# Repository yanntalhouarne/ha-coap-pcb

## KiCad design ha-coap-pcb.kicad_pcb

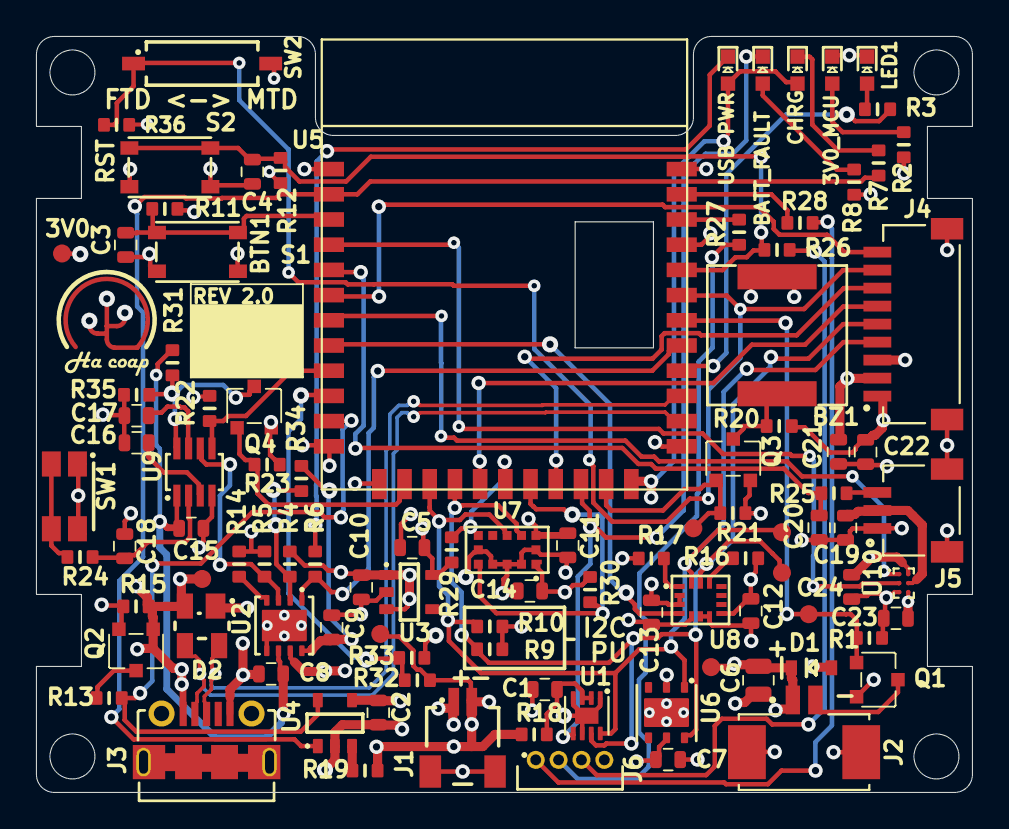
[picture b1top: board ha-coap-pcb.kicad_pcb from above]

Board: 4 copper layers, 52.0 x 42.0 mm, 104 parts (0 on the bottom side), 58 nets.

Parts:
BZ1: CPT-7502-65-SMT-TR; CPT-7502-65-SMT-TR-Footprint-1
C1, C3, C4, C7, C8, C9, C12, C13, C14, C15, C18, C20, C23, C24: C0603C104K5RACTU; C0603
C2, C5, C10, C19, C21, C22: CL10A105KB8NNNC; C0603
C6: GRM21BR61H106KE43L; C0805
C11: CL10A475KP8NNNC; C0603
C16, C17: CC0603KRX7R9BB333; C0603
D1: SD05T1G; SD05T1G-Footprint-1
D2: SP0503BAHTG; SP0503BAHTG-Footprint-1
J1: SM02B-SRSS-TB; FP-SM02B-SRSS-TB_LF_SN-0
J2: 0532610271; 0532610271-Footprint-1
J3: USB-MICRO-1050170001; USB-MICRO-B_V
J4: SM09B-SRSS-TB; SM09B-SRSS-TB-Footprint-1
J5: SM03B-SRSS-TB; SM03B-SRSS-TB-Footprint-1
J6: M50-3930442; FP-M50-3930442-MFG
LED1: LTST-C190GKT; LED-0603
LED2: LTST-C190TBKT; LED-0603
LED3: LTST-C190KRKT; LED-0603
LED4: LTST-C190KFKT; LED-0603
LED5: LTST-C190KSKT; LED-0603
M1, M2, M3, M4: MH-2.5mm-Non-Plated; MH-2.5mm-Non-Plated-Footprint-1
Q1: TSM850N06CX RFG; SOT-23-3
Q2, Q3, Q4: 2N7002P,235; SOT-23-3
R1, R15, R21, R23: RMCF0603FT47K0; R0603
R2, R3, R6, R7, R8, R20, R25: RMCF0603FT1K00; R0603
R4, R5, R11, R12, R22, R29, R30, R33, R34, R36: RMCF0603FT10K0; R0603
R9, R10, R24, R32: RMCF0603FT4K70; R0603
R13: RMCF0603FT2K00; R0603
R14: RMCF0603FG402R; R0603
R16, R17, R18, R19, R26, R27, R28: RMCF0603ZT0R00; R0603
R31: RMCF0603FT330K; R0603
R35: RMCF0603FT76K8; R0603
S1, S2: E-SWITCH_TL3365AF180QG_TACT-SWITCH-SMD; J_E-SWITCH_TL3365AF180QG_TACT-SWITCH-SMD
SW1: EVQ-P7A01P; FP-EVQ-P7A01P-MFG
SW2: TDA01H0SB1R; FP-TDA01H0SB1R-MFG
TP1, TP2, TP3, TP4, TP5, TP6, TP7, TP8: 1MM_PAD_TP; 1MM_PAD_TP-Footprint-1
U1: MAX17048G+T10; 8-WFDFN Exposed Pad
U2: TPS2115ADRBT; 8-VDFN (3x3) w/ EPAD
U3: S-1318D30-M5T1U4; SOT23-5
U4: STC4054GR; SOT23-5
U5: ACN52840; ACN52840-Footprint-1
U6: HDC1080DMBT; FP-DMB0006A-MFG
U7: VL53L0CXV0DH/1; FP-LGA-12-MFG
U8: LSM6DSMTR; 14-LGA (2.5x3mm)
U9: LTC2950CTS8-2#TRMPBF; SOT23-8
U10: FPF1320UCX; 6-WLCSP (0.96x1.66)

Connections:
+VBATT: C8.2, C15.1, J1.2, R18.1, R19.2, R31.2, R32.1, TP1.1, U2.6, U9.1
+VCC: BZ1.1, C6.2, C10.1, C22.1, C24.2, D1.2, J2.1, J4.1, R4.2, R20.2, TP4.1, U2.7, U3.1, U3.3, U10.A2
+VMCU: C5.1, C7.1, C11.1, C12.1, C13.1, C14.1, C21.1, C23.2, J4.2, R2.2, R8.2, R9.2, R10.2, R11.2, R12.2, R16.2, R22.2, R29.1, R30.2, R36.1, TP5.1, U3.5, U5.12, U5.24, U5.32, U6.5, U7.1, U7.11, U8.5, U8.8, U10.C2
+VSENSOR: C19.1, J5.2, U10.B2
+VUSB: C2.1, C9.2, D2.2, J3.1, LED4.2, LED5.2, Q2.1, R15.2, R34.2, TP6.1, U2.8, U4.4, U5.23
ALERTn: LED3.1, U1.5, U5.21
AN0: C20.2, R25.1, U5.5
AN1: J4.9, U5.6
BTN: C3.1, R11.1, S1.3, S1.4, U5.3
BUZZER: Q3.1, R21.1, TP8.1, U5.22
CHRGn: R7.2, U4.1, U5.2
D_N: D2.3, J3.2, U5.25
D_P: D2.4, J3.3, U5.26
GND: C1.2, C2.2, C3.2, C4.2, C5.2, C6.1, C7.2, C8.1, C9.1, C10.2, C11.2, C12.2, C13.2, C14.2, C15.2, C16.1, C17.1, C18.2, C19.2, C20.1, C21.2, C22.2, C23.1, C24.1, D1.1, D2.1, J1.1, J1.S1, J1.S2, J2.S1, J2.S2, J3.5, J3.6, J3.7, J3.8, J3.9, J3.10, J3.11, J4.3, J4.S1, J4.S2, J5.1, J5.S1, J5.S2, J6.4, LED1.1, LED2.1, Q1.2, Q2.2, Q3.2, Q4.2, R1.1, R5.2, R14.1, R15.1, R17.1, R21.2, R23.2, R33.1, R35.1, S1.1, S1.2, S2.1, S2.2, SW1.1, SW1.1', SW2.2, U1.1, U1.4, U1.6, U1.9, U2.5, U2.9, U3.2, U4.2, U5.1, U5.13, U5.35, U6.2, U7.2, U7.3, U7.4, U7.6, U7.12, U8.2, U8.3, U8.6, U8.7, U9.4, U10.C1
GPIO_0_24: J4.8, R36.2, SW2.1, U5.30
IMU_INT1: U5.8, U8.4
I_BATT: R13.2, U4.5, U5.11
LED_BLUE: R3.2, U5.27
NetBZ1_2: BZ1.2, Q3.3, R20.1
NetC1_1: C1.1, R18.2, U1.2, U1.3
NetC16_2: C16.2, U9.3
NetC17_2: C17.2, U9.7
NetJ2_2: J2.2, Q1.3
NetJ5_3: J5.3, R25.2
NetJ6_1: J6.1, R28.2
NetJ6_2: J6.2, R27.2
NetJ6_3: J6.3, R26.2
NetLED1_2: LED1.2, R2.1
NetLED2_2: LED2.2, R3.1
NetLED3_2: LED3.2, R8.1
NetLED4_1: LED4.1, R7.1
NetLED5_1: LED5.1, R6.1
NetQ2_3: Q2.3, R13.1
NetQ4_3: Q4.3, R31.1, R35.2, U9.8
NetR14_2: R14.2, U2.4
NetR16_1: R16.1, U8.12
NetR17_2: R17.2, U8.1
NetR19_1: R19.1, U4.3
NetR24_1: R24.1, SW1.2, SW1.2'
PWR_BTN_INTn: R22.1, U5.9, U9.5
PWR_BTNn: C18.1, R24.2, U9.2
PWR_KILL: Q4.1, R23.1, U5.14
PWR_SW: Q1.1, R1.2, TP7.1, U5.29
RESET: C4.1, R12.1, R26.1, S2.3, S2.4, U5.31
SCL: J4.5, R9.1, TP2.1, U1.7, U5.16, U6.6, U7.10, U8.13
SDA: J4.4, R10.1, TP3.1, U1.8, U5.15, U6.1, U7.9, U8.14
SENSOR_EN: U5.7, U10.A1
SWDCLK: R28.1, U5.34
SWDIO: R27.1, U5.33
SW_D0: R4.1, R34.1, U2.2
SW_D1: R5.1, U2.3, U9.6
TOF_INT: R29.2, U5.18, U7.7
TOF_SHNn: R30.1, U5.19, U7.5
UART_RX: J4.7, U5.20
UART_TX: J4.6, U5.17
USB_PWR: R6.2, U2.1, U5.28
VS_SEL: U5.4, U10.B1
V_BAT: R32.2, R33.2, U5.10

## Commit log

2025-04-14 Exported PCB file from Altium.
